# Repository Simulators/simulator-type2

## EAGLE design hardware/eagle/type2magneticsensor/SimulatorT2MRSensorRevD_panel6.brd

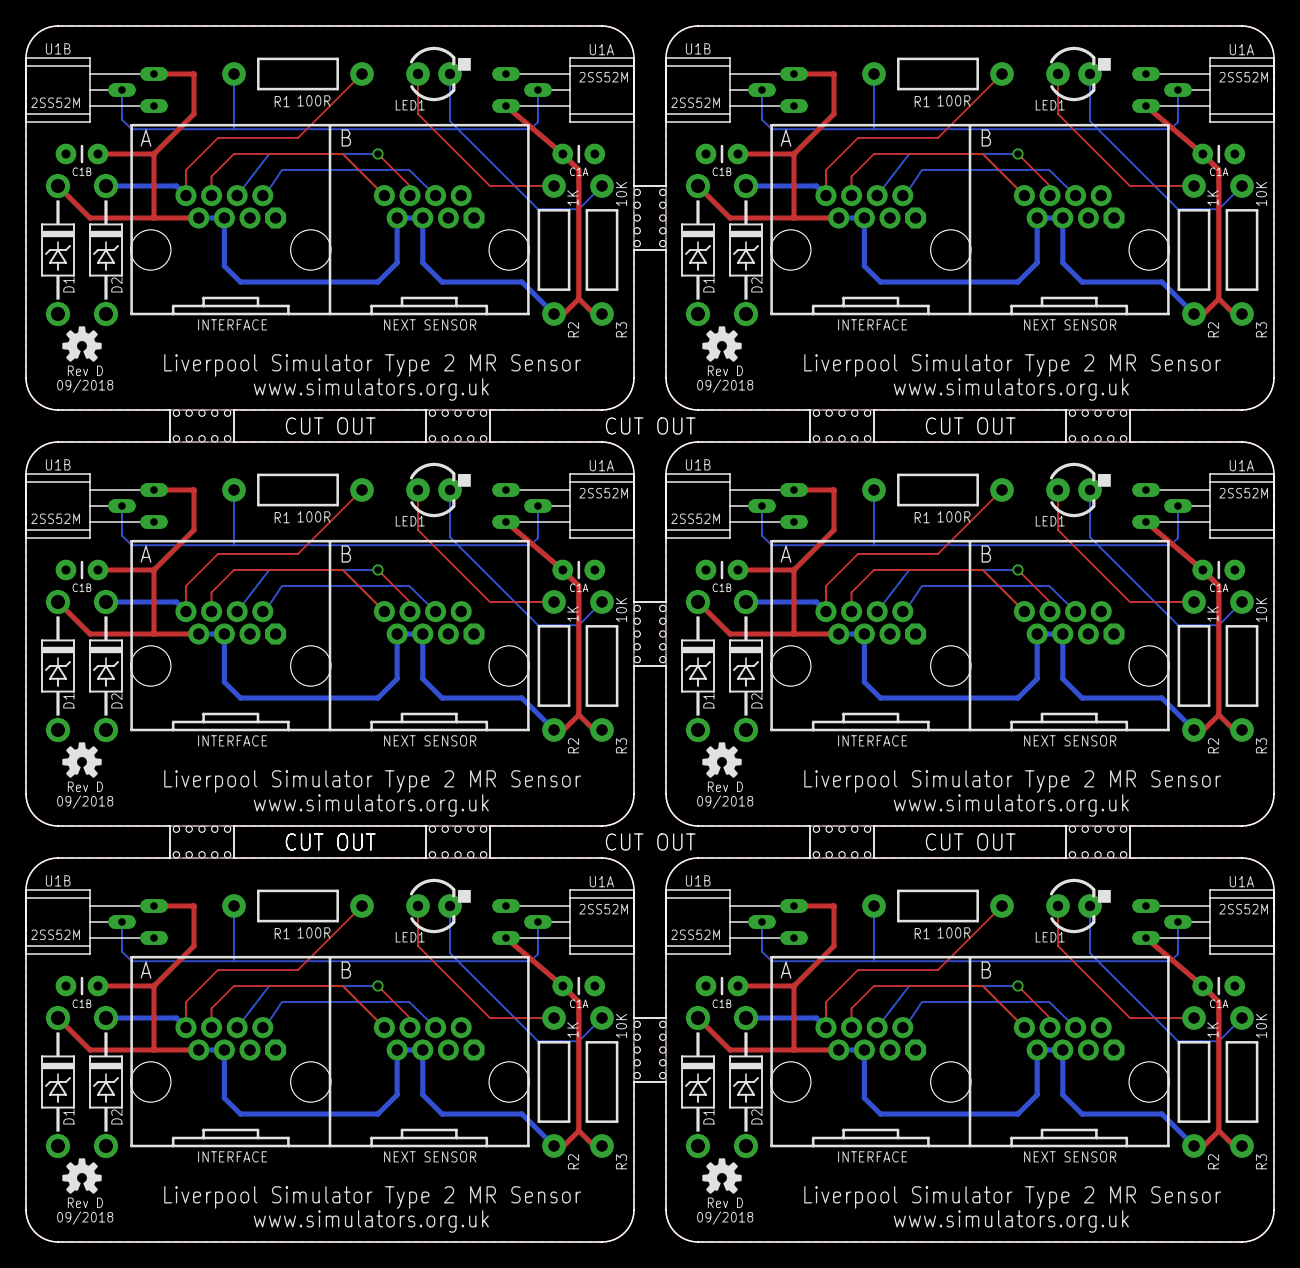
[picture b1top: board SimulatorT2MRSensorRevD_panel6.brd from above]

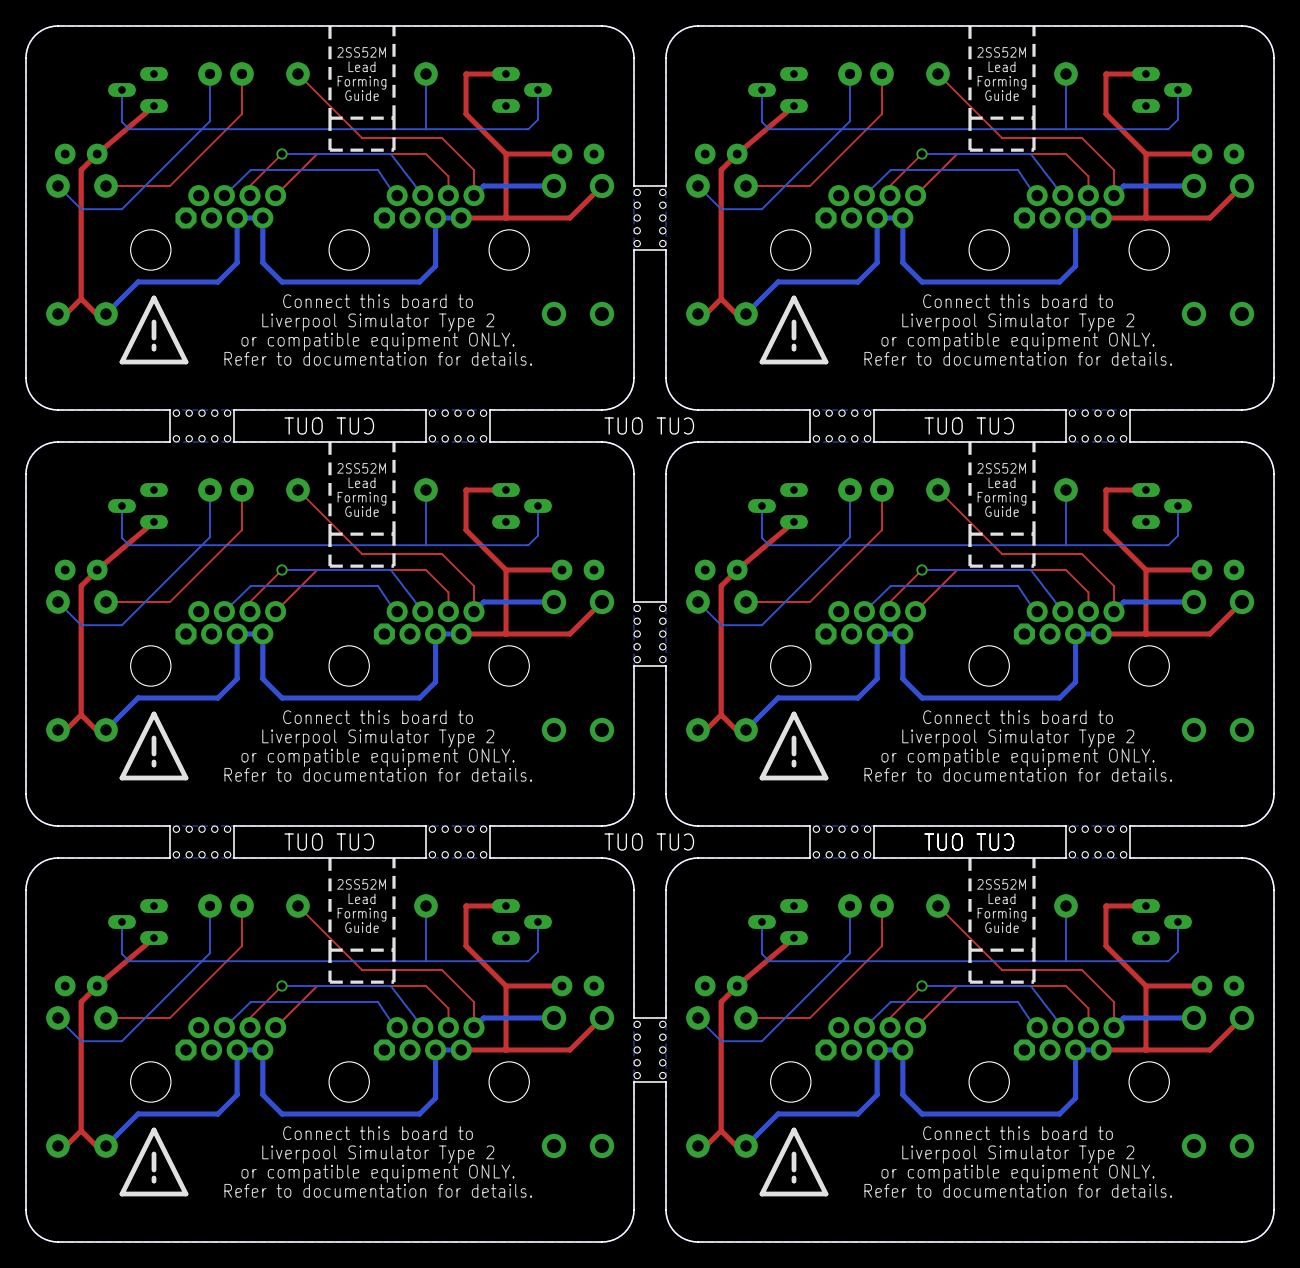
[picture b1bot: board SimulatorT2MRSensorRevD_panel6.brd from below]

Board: 2 copper layers, 99.1 x 96.5 mm, 79 parts (6 on the bottom side), 48 nets.

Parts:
C1A, C1A_1, C1A_2, C1A_3, C1A_4, C1A_5, C1B, C1B_1, C1B_2, C1B_3, C1B_4, C1B_5: 100nF; CAP-PTH-SMALL
D1, D1_1, D1_2, D1_3, D1_4, D1_5, D2, D2_1, D2_2, D2_3, D2_4, D2_5: SA5.0A; DO41_TVS_UNI
E$1, E$2, E$3, E$4, E$5, E$6: WARNING_TRIANGLE_TPLACE
E$12: OUTLINE_PANEL_6_5MM
JP1, JP1_1, JP1_2, JP1_3, JP1_4, JP1_5: RJ45-RJHSE-5080-023HOLE; RJ45-RJHSE-5080-02-3HOLE
LED1, LED1_1, LED1_2, LED1_3, LED1_4, LED1_5: Blue; LED3MM
LOGO1, LOGO1_1, LOGO1_2, LOGO1_3, LOGO1_4, LOGO1_5: OSHW-LOGOS; OSHW-LOGO-S
R1, R1_1, R1_2, R1_3, R1_4, R1_5: 100R; AXIAL-0.4
R2, R2_1, R2_2, R2_3, R2_4, R2_5: 1K; AXIAL-0.4
R3, R3_1, R3_2, R3_3, R3_4, R3_5: 10K; AXIAL-0.4
U1A, U1A_1, U1A_2, U1A_3, U1A_4, U1A_5, U1B, U1B_1, U1B_2, U1B_3, U1B_4, U1B_5: 2SS52MOFFSET; 2SS52M_FLAT_OFFSET

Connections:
!OUT!: D2.CATHODE, JP1.A8, R1.P$1
!OUT!1: D2_1.CATHODE, JP1_1.A8, R1_1.P$1
!OUT!2: D2_2.CATHODE, JP1_2.A8, R1_2.P$1
!OUT!3: D2_3.CATHODE, JP1_3.A8, R1_3.P$1
!OUT!4: D2_4.CATHODE, JP1_4.A8, R1_4.P$1
!OUT!5: D2_5.CATHODE, JP1_5.A8, R1_5.P$1
B2: JP1.A6, JP1.B8
B3: JP1.A4, JP1.B6
B4: JP1.A2, JP1.B4
B21: JP1_1.A6, JP1_1.B8
B22: JP1_2.A6, JP1_2.B8
B23: JP1_3.A6, JP1_3.B8
B24: JP1_4.A6, JP1_4.B8
B25: JP1_5.A6, JP1_5.B8
B31: JP1_1.A4, JP1_1.B6
B32: JP1_2.A4, JP1_2.B6
B33: JP1_3.A4, JP1_3.B6
B34: JP1_4.A4, JP1_4.B6
B35: JP1_5.A4, JP1_5.B6
B41: JP1_1.A2, JP1_1.B4
B42: JP1_2.A2, JP1_2.B4
B43: JP1_3.A2, JP1_3.B4
B44: JP1_4.A2, JP1_4.B4
B45: JP1_5.A2, JP1_5.B4
GND: C1A.2, C1B.2, D1.ANODE, D2.ANODE, JP1.A1, JP1.A3, JP1.B1, JP1.B3, U1A.P$1, U1B.P$1
GND1: C1A_1.2, C1B_1.2, D1_1.ANODE, D2_1.ANODE, JP1_1.A1, JP1_1.A3, JP1_1.B1, JP1_1.B3, U1A_1.P$1, U1B_1.P$1
GND2: C1A_2.2, C1B_2.2, D1_2.ANODE, D2_2.ANODE, JP1_2.A1, JP1_2.A3, JP1_2.B1, JP1_2.B3, U1A_2.P$1, U1B_2.P$1
GND3: C1A_3.2, C1B_3.2, D1_3.ANODE, D2_3.ANODE, JP1_3.A1, JP1_3.A3, JP1_3.B1, JP1_3.B3, U1A_3.P$1, U1B_3.P$1
GND4: C1A_4.2, C1B_4.2, D1_4.ANODE, D2_4.ANODE, JP1_4.A1, JP1_4.A3, JP1_4.B1, JP1_4.B3, U1A_4.P$1, U1B_4.P$1
GND5: C1A_5.2, C1B_5.2, D1_5.ANODE, D2_5.ANODE, JP1_5.A1, JP1_5.A3, JP1_5.B1, JP1_5.B3, U1A_5.P$1, U1B_5.P$1
LED: LED1.A, R2.P$1
LED1: LED1_1.A, R2_1.P$1
LED2: LED1_2.A, R2_2.P$1
LED3: LED1_3.A, R2_3.P$1
LED4: LED1_4.A, R2_4.P$1
LED5: LED1_5.A, R2_5.P$1
SIG: LED1.K, R1.P$2, R3.P$1, U1A.P$2, U1B.P$2
SIG1: LED1_1.K, R1_1.P$2, R3_1.P$1, U1A_1.P$2, U1B_1.P$2
SIG2: LED1_2.K, R1_2.P$2, R3_2.P$1, U1A_2.P$2, U1B_2.P$2
SIG3: LED1_3.K, R1_3.P$2, R3_3.P$1, U1A_3.P$2, U1B_3.P$2
SIG4: LED1_4.K, R1_4.P$2, R3_4.P$1, U1A_4.P$2, U1B_4.P$2
SIG5: LED1_5.K, R1_5.P$2, R3_5.P$1, U1A_5.P$2, U1B_5.P$2
VCC: C1A.1, C1B.1, D1.CATHODE, JP1.A5, JP1.A7, JP1.B5, JP1.B7, R2.P$2, R3.P$2, U1A.P$3, U1B.P$3
VCC1: C1A_1.1, C1B_1.1, D1_1.CATHODE, JP1_1.A5, JP1_1.A7, JP1_1.B5, JP1_1.B7, R2_1.P$2, R3_1.P$2, U1A_1.P$3, U1B_1.P$3
VCC2: C1A_2.1, C1B_2.1, D1_2.CATHODE, JP1_2.A5, JP1_2.A7, JP1_2.B5, JP1_2.B7, R2_2.P$2, R3_2.P$2, U1A_2.P$3, U1B_2.P$3
VCC3: C1A_3.1, C1B_3.1, D1_3.CATHODE, JP1_3.A5, JP1_3.A7, JP1_3.B5, JP1_3.B7, R2_3.P$2, R3_3.P$2, U1A_3.P$3, U1B_3.P$3
VCC4: C1A_4.1, C1B_4.1, D1_4.CATHODE, JP1_4.A5, JP1_4.A7, JP1_4.B5, JP1_4.B7, R2_4.P$2, R3_4.P$2, U1A_4.P$3, U1B_4.P$3
VCC5: C1A_5.1, C1B_5.1, D1_5.CATHODE, JP1_5.A5, JP1_5.A7, JP1_5.B5, JP1_5.B7, R2_5.P$2, R3_5.P$2, U1A_5.P$3, U1B_5.P$3

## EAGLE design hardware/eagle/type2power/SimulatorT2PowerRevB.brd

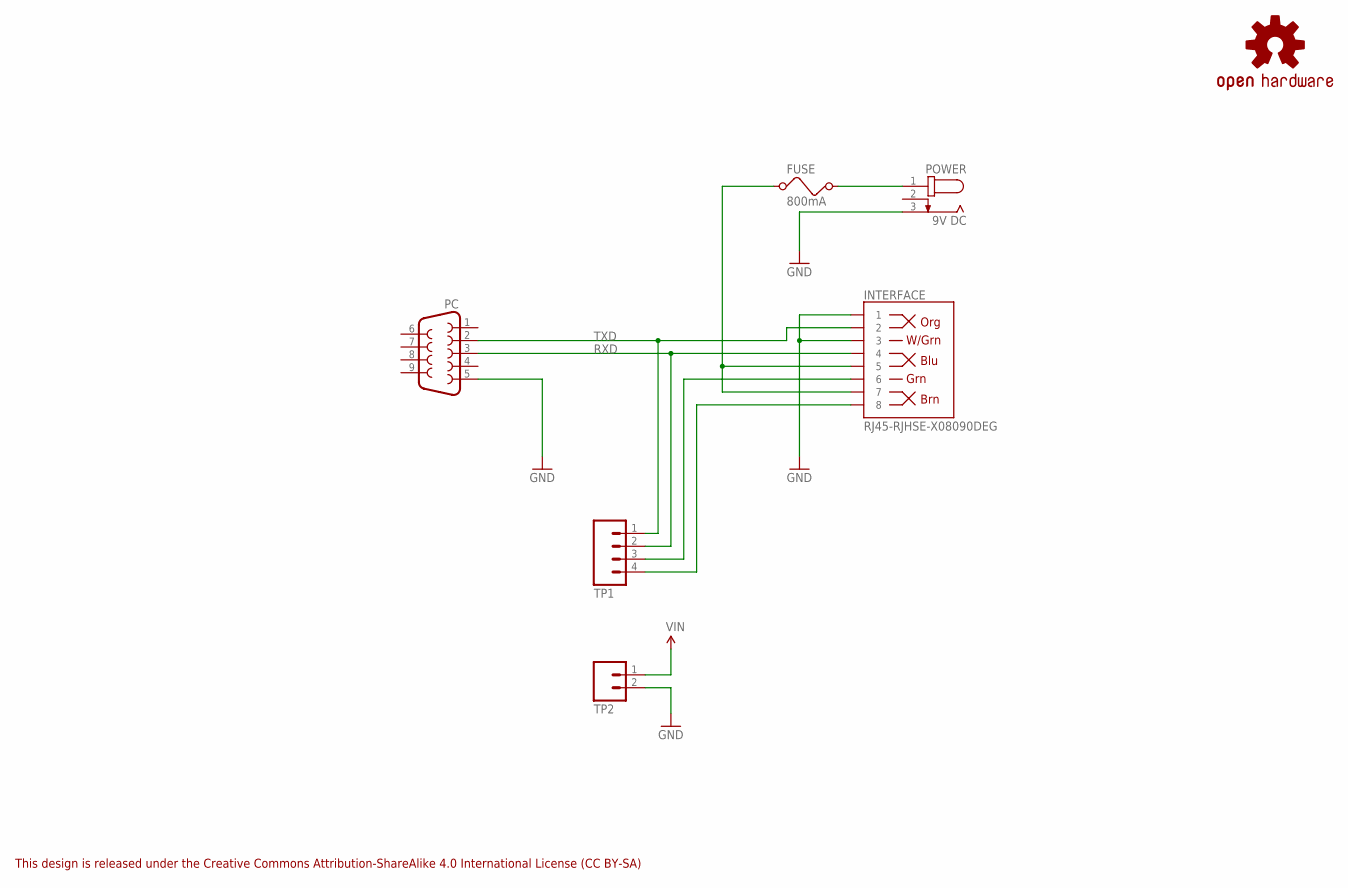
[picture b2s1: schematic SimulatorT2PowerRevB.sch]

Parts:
FUSE: 800mA; MCOMP-FUSE-HOLDER-PCB
INTERFACE: RJ45-RJHSE-X08090DEG; RJ45-RJHSE-5080
LOGO1: OSHW-LOGOS; OSHW-LOGO-S
PC: DB9-CONNECTOR-PCBFEMALE; MULTICOMP-DB9-FEMALE-PCB-90DEG
POWER: 9V DC; CLIFF-FC681465P-DC-JACK
TP1: M04PTH; 1X04
TP2: M02PTH; 1X02

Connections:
GND: INTERFACE.1, INTERFACE.3, PC.5, POWER.3, TP2.2
P6: INTERFACE.6, TP1.3
P8: INTERFACE.8, TP1.4
RXD: INTERFACE.4, PC.3, TP1.2
TXD: INTERFACE.2, PC.2, TP1.1
VIN: FUSE.2, POWER.1, TP2.1
VIN2: FUSE.1, INTERFACE.5, INTERFACE.7

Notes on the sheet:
This design is released under the Creative Commons Attribution-ShareAlike 4.0 International License (CC BY-SA)

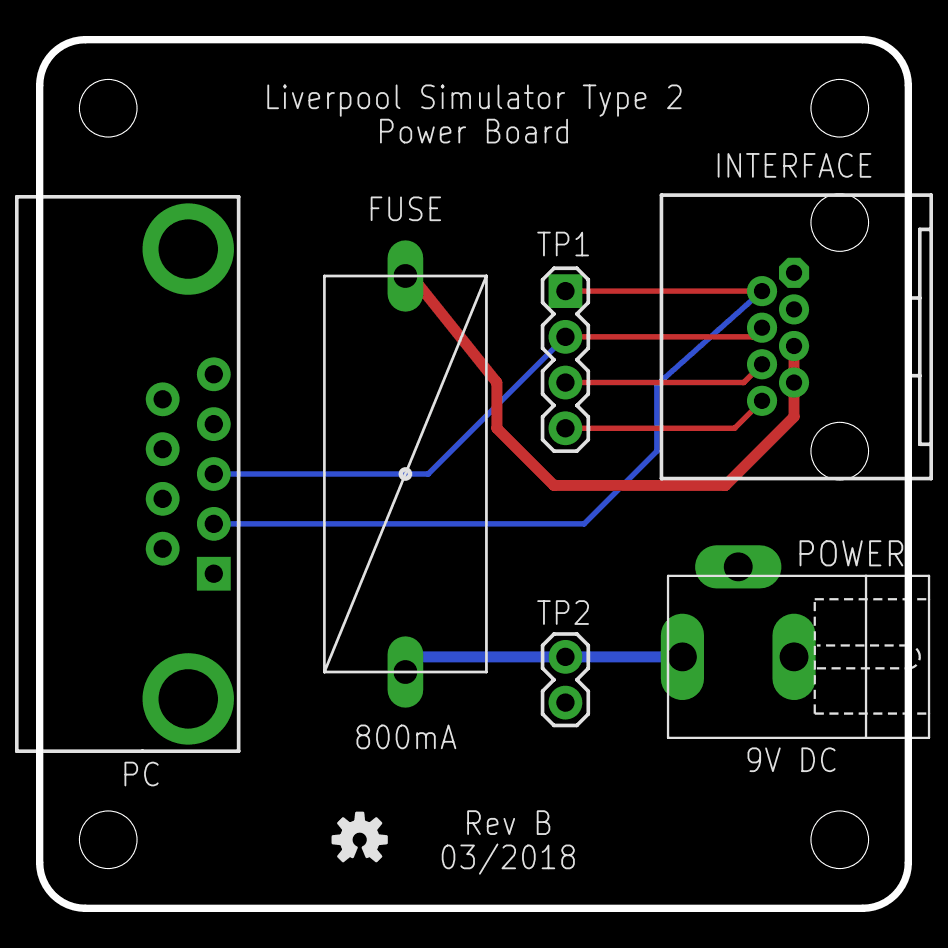
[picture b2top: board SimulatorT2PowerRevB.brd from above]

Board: 2 copper layers, 48.3 x 48.3 mm, 7 parts (0 on the bottom side), 7 nets.

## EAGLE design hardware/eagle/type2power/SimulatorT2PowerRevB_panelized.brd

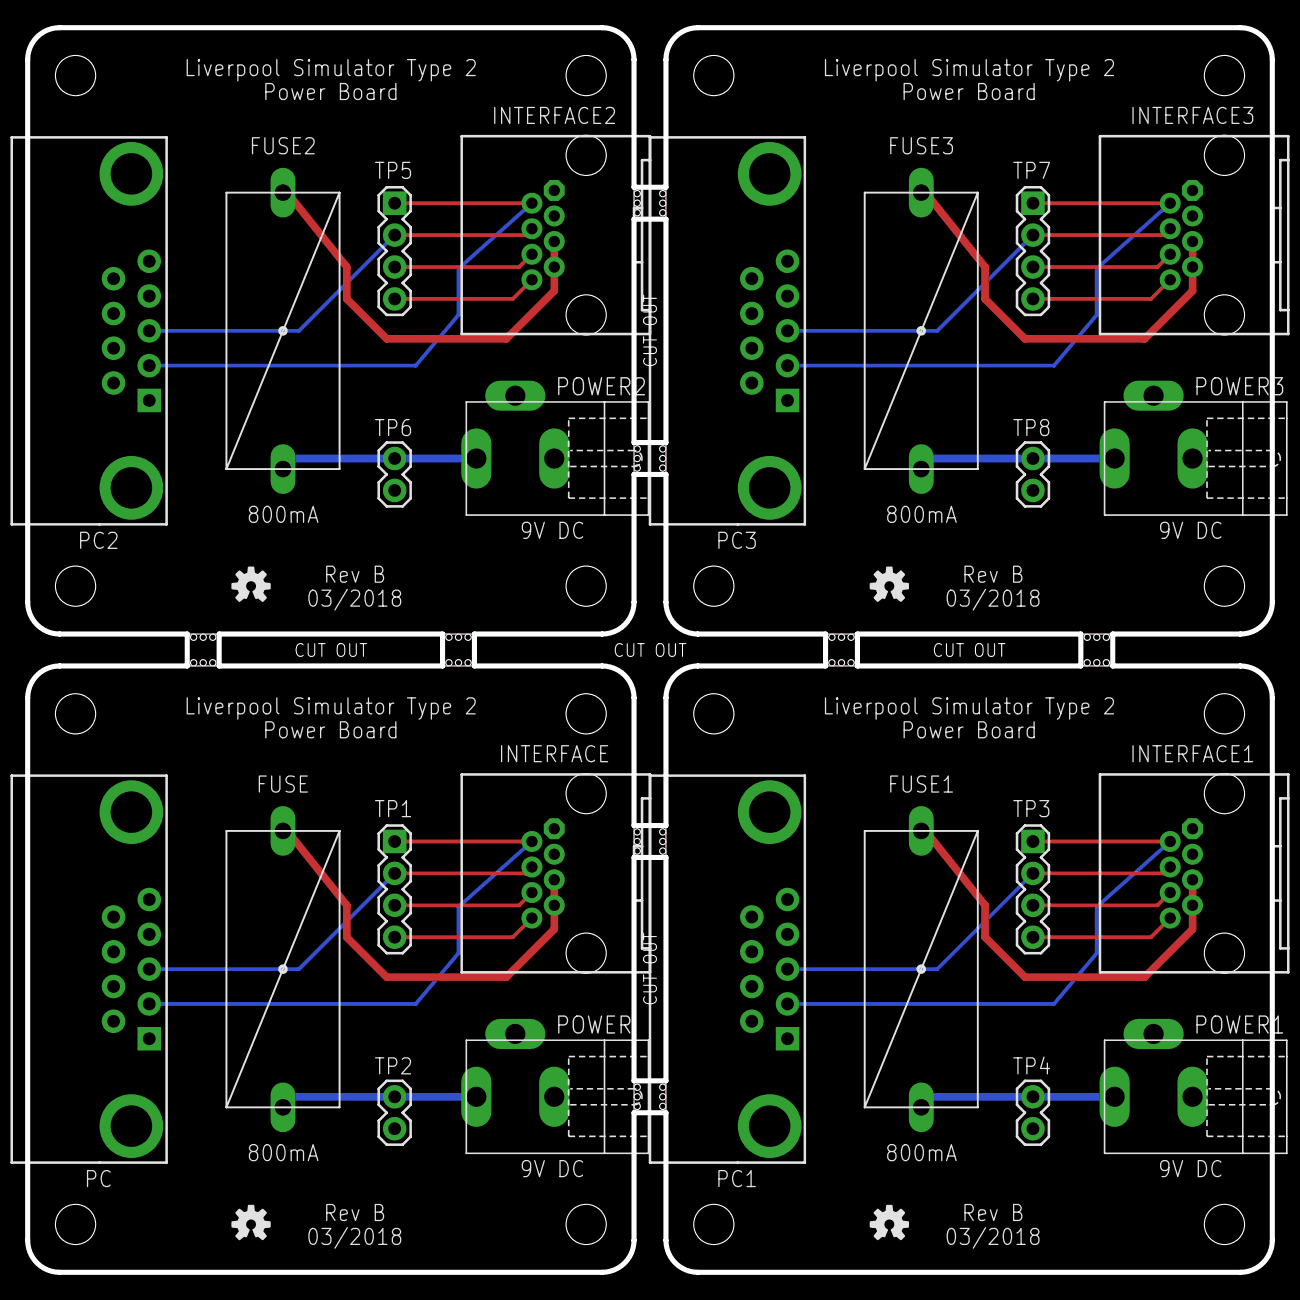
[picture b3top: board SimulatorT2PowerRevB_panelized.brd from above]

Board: 2 copper layers, 99.1 x 99.1 mm, 36 parts (0 on the bottom side), 28 nets.

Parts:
E$1, E$2, E$3, E$4, E$5, E$6, E$7, E$8: STAMP_HOLES
FUSE, FUSE1, FUSE2, FUSE3: 800mA; MCOMP-FUSE-HOLDER-PCB
INTERFACE, INTERFACE1, INTERFACE2, INTERFACE3: RJ45-RJHSE-X08090DEG; RJ45-RJHSE-5080
LOGO1, LOGO2, LOGO3, LOGO4: OSHW-LOGOS; OSHW-LOGO-S
PC, PC1, PC2, PC3: MULTICOMP-DB9-FEMALE-PCB-90DEG
POWER, POWER1, POWER2, POWER3: 9V DC; CLIFF-FC681465P-DC-JACK
TP1, TP3, TP5, TP7: 1X04
TP2, TP4, TP6, TP8: 1X02

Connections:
GND: INTERFACE.1, INTERFACE.3, PC.5, POWER.3, TP2.2
GND1: INTERFACE1.1, INTERFACE1.3, PC1.5, POWER1.3, TP4.2
GND2: INTERFACE2.1, INTERFACE2.3, PC2.5, POWER2.3, TP6.2
GND3: INTERFACE3.1, INTERFACE3.3, PC3.5, POWER3.3, TP8.2
P1: INTERFACE1.6, TP3.3
P2: INTERFACE1.8, TP3.4
P3: INTERFACE2.6, TP5.3
P4: INTERFACE2.8, TP5.4
P5: INTERFACE3.6, TP7.3
P6: INTERFACE.6, TP1.3
P7: INTERFACE3.8, TP7.4
P8: INTERFACE.8, TP1.4
RXD: INTERFACE.4, PC.3, TP1.2
RXD1: INTERFACE1.4, PC1.3, TP3.2
RXD2: INTERFACE2.4, PC2.3, TP5.2
RXD3: INTERFACE3.4, PC3.3, TP7.2
TXD: INTERFACE.2, PC.2, TP1.1
TXD1: INTERFACE1.2, PC1.2, TP3.1
TXD2: INTERFACE2.2, PC2.2, TP5.1
TXD3: INTERFACE3.2, PC3.2, TP7.1
VIN: FUSE.2, POWER.1, TP2.1
VIN1: FUSE1.2, POWER1.1, TP4.1
VIN2: FUSE.1, INTERFACE.5, INTERFACE.7
VIN3: FUSE1.1, INTERFACE1.5, INTERFACE1.7
VIN4: FUSE2.2, POWER2.1, TP6.1
VIN5: FUSE2.1, INTERFACE2.5, INTERFACE2.7
VIN6: FUSE3.2, POWER3.1, TP8.1
VIN7: FUSE3.1, INTERFACE3.5, INTERFACE3.7

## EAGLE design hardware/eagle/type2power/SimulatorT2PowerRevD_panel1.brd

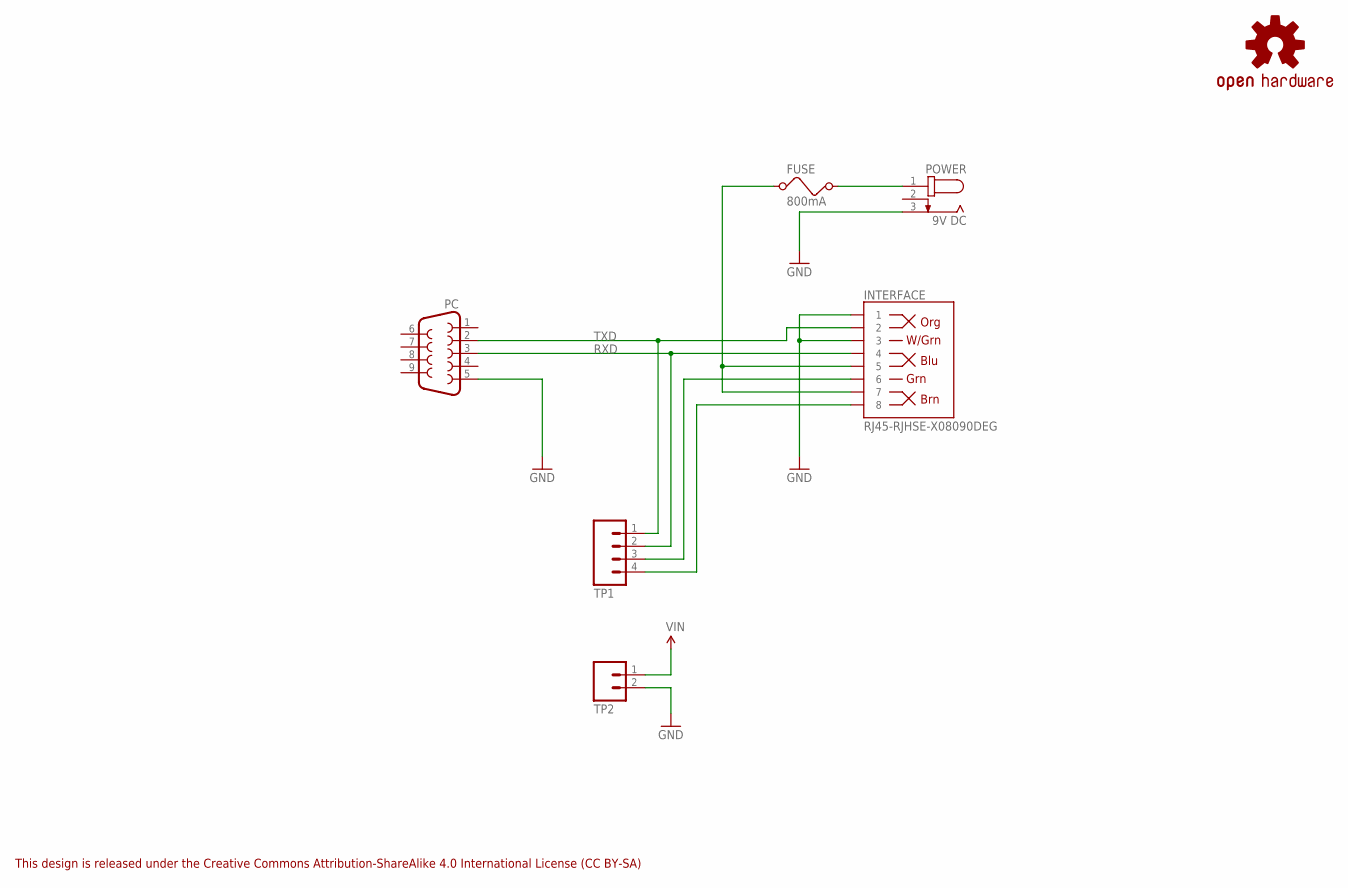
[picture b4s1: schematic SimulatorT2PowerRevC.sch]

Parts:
FUSE: 800mA; MCOMP-FUSE-HOLDER-PCB
INTERFACE: RJ45-RJHSE-X08090DEG; RJ45-RJHSE-5080
LOGO1: OSHW-LOGOS; OSHW-LOGO-S
PC: DB9-CONNECTOR-PCBFEMALE; MULTICOMP-DB9-FEMALE-PCB-90DEG
POWER: 9V DC; CLIFF-FC681465P-DC-JACK
TP1: M04PTH; 1X04
TP2: M02PTH; 1X02

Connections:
GND: INTERFACE.1, INTERFACE.3, PC.5, POWER.3, TP2.2; also elsewhere on the board
P8: INTERFACE.8, TP1.4
RXD: INTERFACE.4, PC.3, TP1.2; also elsewhere on the board
TX2: INTERFACE.6, TP1.3; also elsewhere on the board
TXD: INTERFACE.2, PC.2, TP1.1; also elsewhere on the board
VIN: FUSE.2, POWER.1, TP2.1
VIN2: FUSE.1, INTERFACE.5, INTERFACE.7; also elsewhere on the board

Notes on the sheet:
This design is released under the Creative Commons Attribution-ShareAlike 4.0 International License (CC BY-SA)

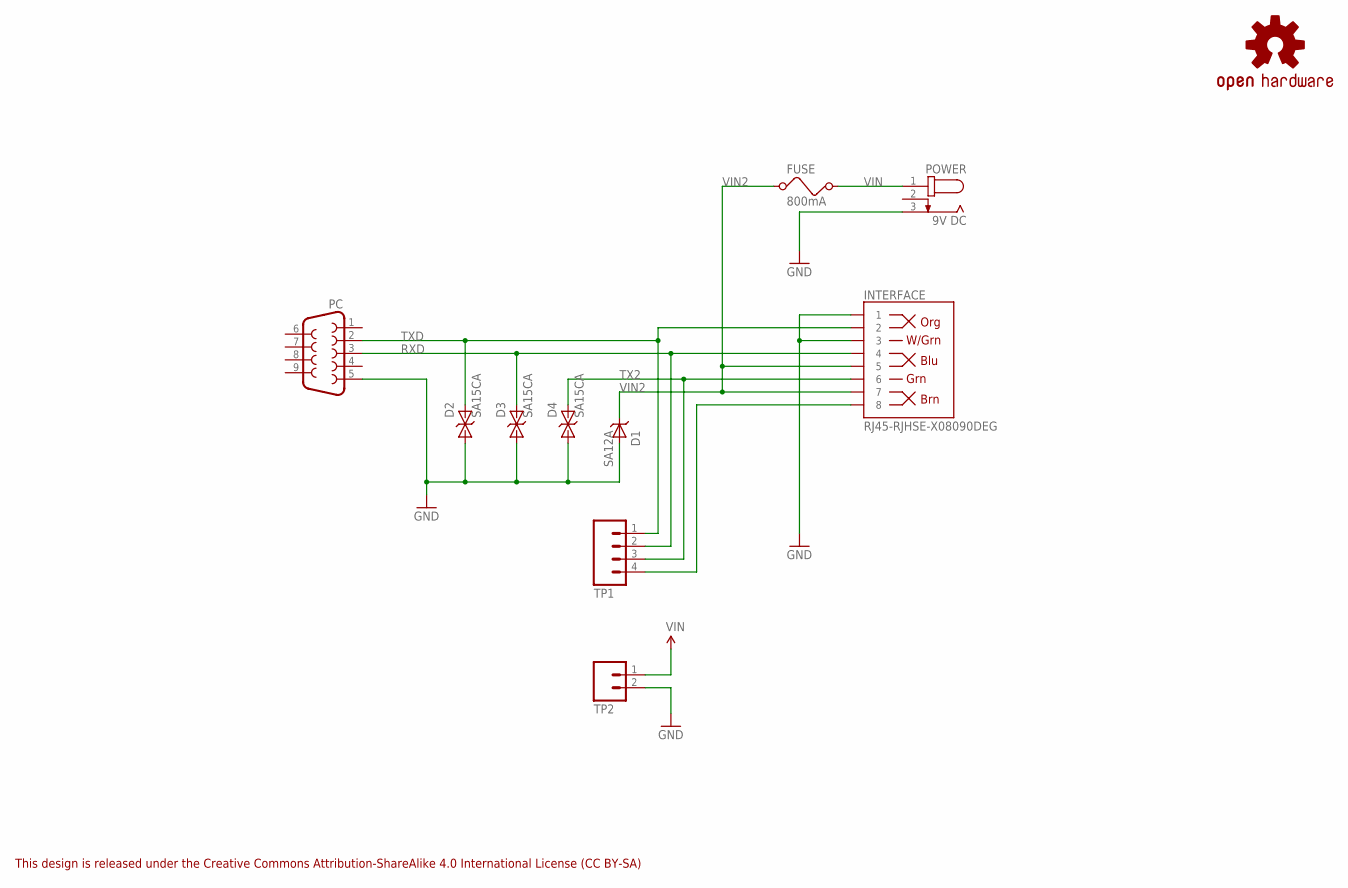
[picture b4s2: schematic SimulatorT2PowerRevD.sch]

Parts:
D1: SA12A; DO41_TVS_UNI
D2, D3, D4: SA15CA; DO41_TVS_BI
FUSE: 800mA; MCOMP-FUSE-HOLDER-PCB
INTERFACE: RJ45-RJHSE-X08090DEG; RJ45-RJHSE-5080
LOGO1: OSHW-LOGOS; OSHW-LOGO-S
PC: DB9-CONNECTOR-PCBFEMALE; MULTICOMP-DB9-FEMALE-PCB-90DEG
POWER: 9V DC; CLIFF-FC681465P-DC-JACK
TP1: M04PTH; 1X04
TP2: M02PTH; 1X02

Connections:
GND: D1.ANODE, D2.A, D3.A, D4.A, INTERFACE.1, INTERFACE.3, PC.5, POWER.3, TP2.2
P8: INTERFACE.8, TP1.4
RXD: D3.C, INTERFACE.4, PC.3, TP1.2
TX2: D4.C, INTERFACE.6, TP1.3
TXD: D2.C, INTERFACE.2, PC.2, TP1.1
VIN: FUSE.2, POWER.1, TP2.1
VIN2: D1.CATHODE, FUSE.1, INTERFACE.5, INTERFACE.7

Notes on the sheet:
This design is released under the Creative Commons Attribution-ShareAlike 4.0 International License (CC BY-SA)

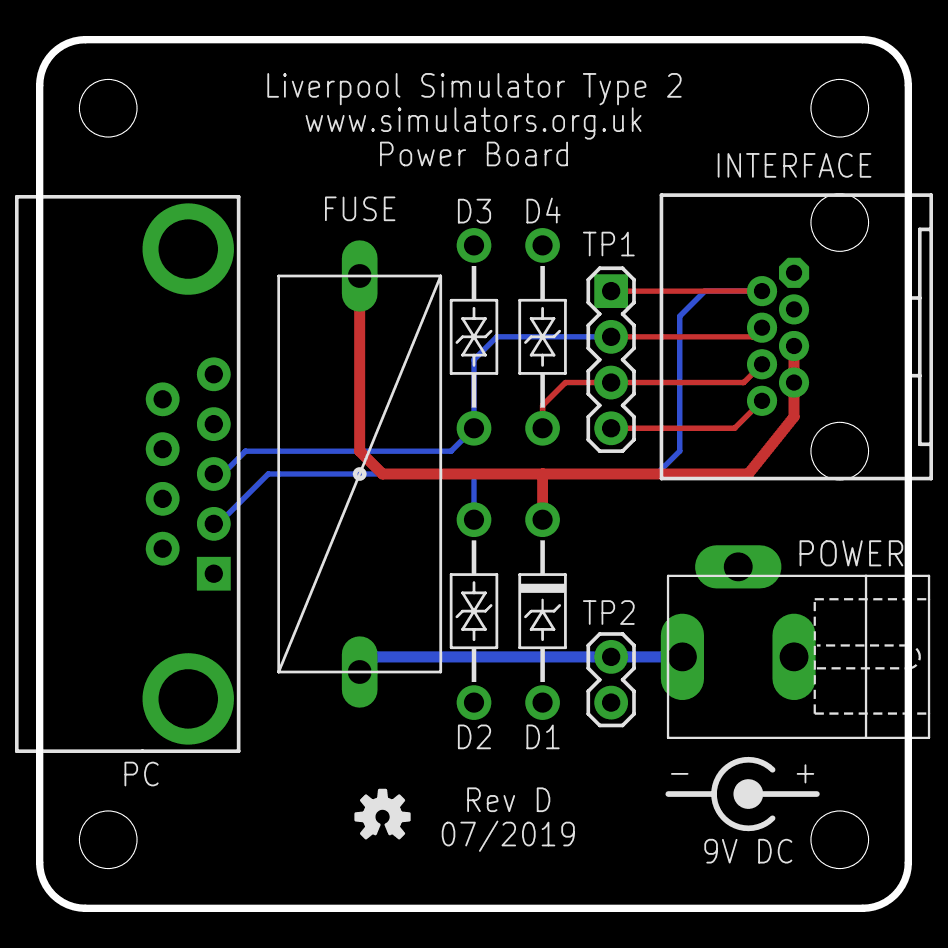
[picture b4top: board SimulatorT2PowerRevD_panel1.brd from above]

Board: 2 copper layers, 48.3 x 48.3 mm, 13 parts (1 on the bottom side), 7 nets.

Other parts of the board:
E$1: WARNING_TRIANGLE_TPLACE
U$1: CENTRE-POS-SILK

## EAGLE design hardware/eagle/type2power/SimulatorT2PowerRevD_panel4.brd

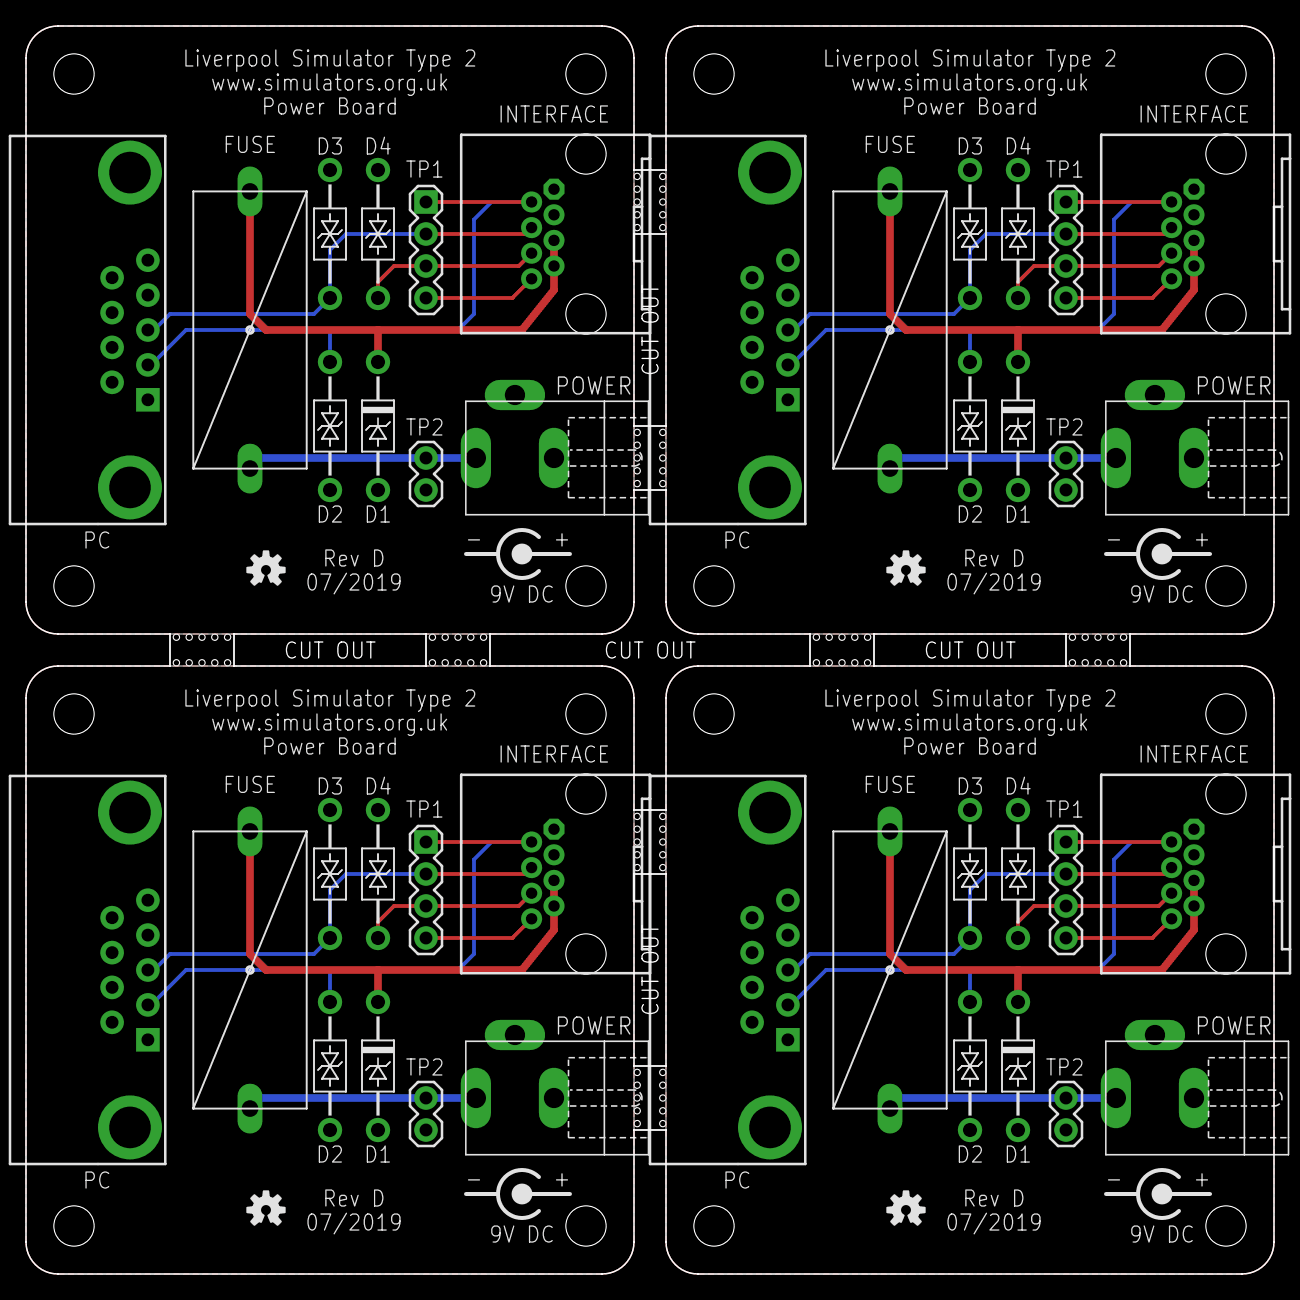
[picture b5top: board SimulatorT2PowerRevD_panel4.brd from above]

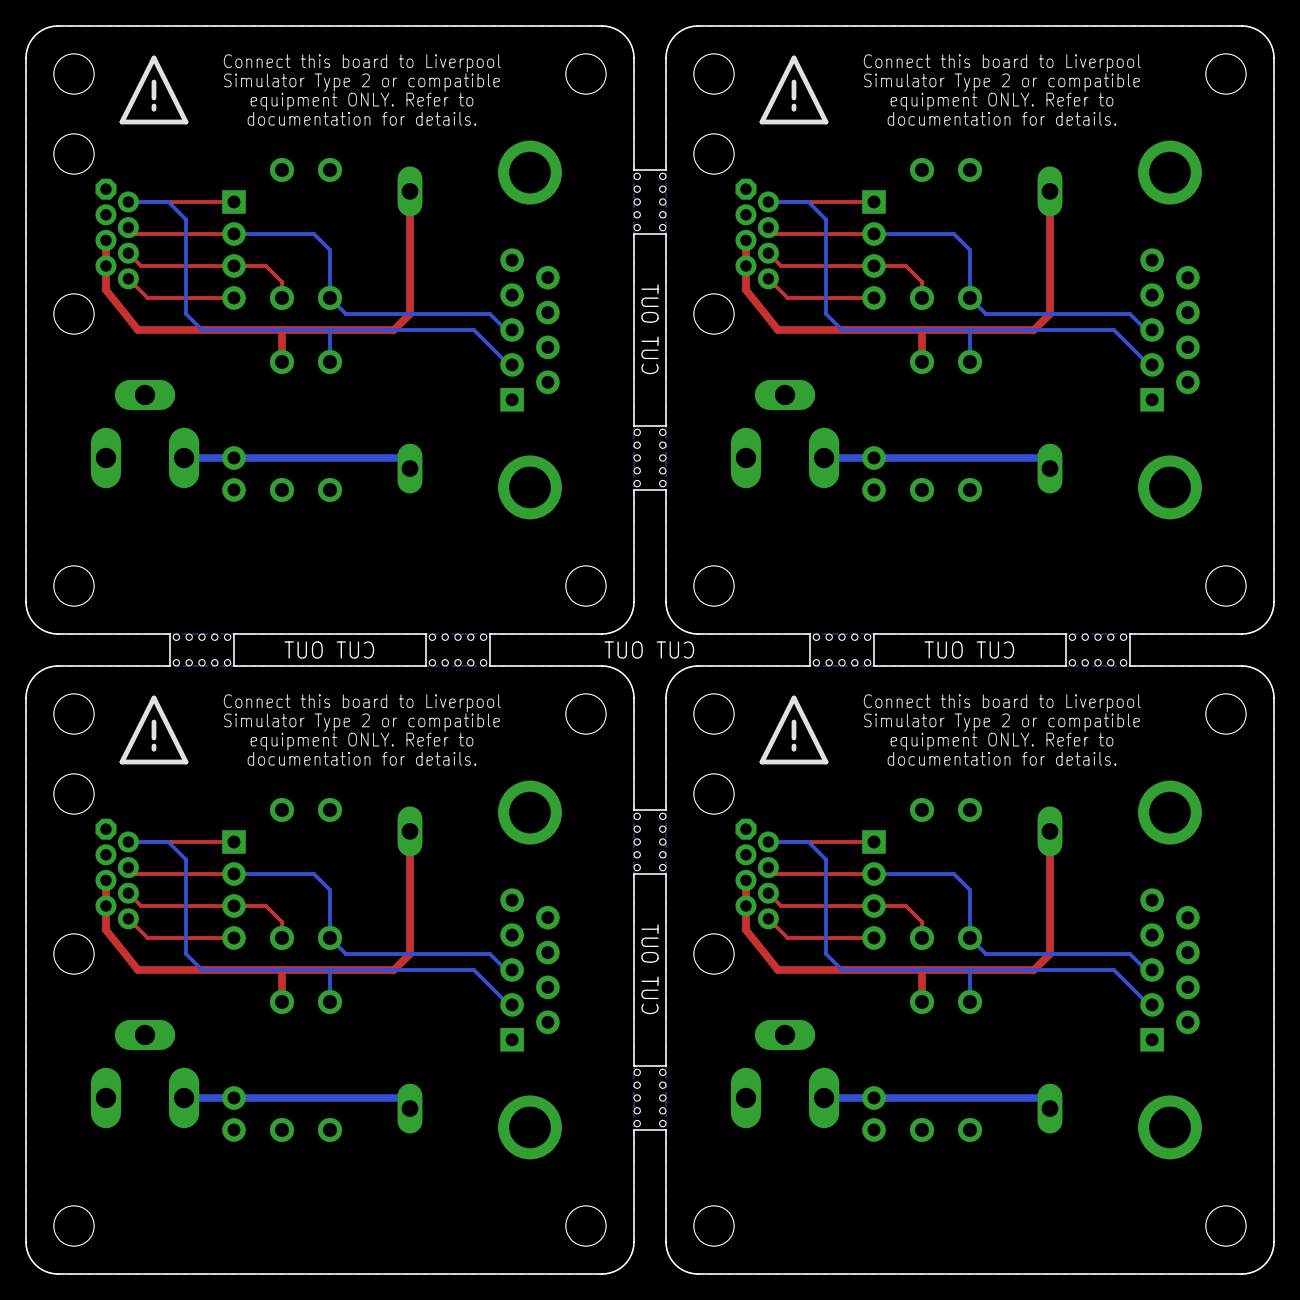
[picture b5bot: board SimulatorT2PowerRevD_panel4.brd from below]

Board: 2 copper layers, 99.1 x 99.1 mm, 53 parts (4 on the bottom side), 28 nets.

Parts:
D1, D1_1, D1_2, D1_3: SA12A; DO41_TVS_UNI
D2, D2_1, D2_2, D2_3, D3, D3_1, D3_2, D3_3, D4, D4_1, D4_2, D4_3: SA15CA; DO41_TVS_BI
E$1, E$3, E$4, E$5: WARNING_TRIANGLE_TPLACE
E$2: OUTLINE_PANEL_4_5MM
FUSE: 800mA; MCOMP-FUSE-HOLDER-PCB
FUSE_1, FUSE_2, FUSE_3: 800mA; MCOMP-FUSE-HOLDER-PCB
INTERFACE: RJ45-RJHSE-X08090DEG; RJ45-RJHSE-5080
INTERFACE_1, INTERFACE_2, INTERFACE_3: RJ45-RJHSE-X08090DEG; RJ45-RJHSE-5080
LOGO1, LOGO1_1, LOGO1_2, LOGO1_3: OSHW-LOGOS; OSHW-LOGO-S
PC: MULTICOMP-DB9-FEMALE-PCB-90DEG
PC_1, PC_2, PC_3: MULTICOMP-DB9-FEMALE-PCB-90DEG
POWER: 9V DC; CLIFF-FC681465P-DC-JACK
POWER_1, POWER_2, POWER_3: 9V DC; CLIFF-FC681465P-DC-JACK
TP1, TP1_1, TP1_2, TP1_3: 1X04
TP2, TP2_1, TP2_2, TP2_3: 1X02
U$1, U$1_1, U$1_2, U$1_3: CENTRE-POS-SILK

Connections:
GND: D1.ANODE, D2.A, D3.A, D4.A, INTERFACE.1, INTERFACE.3, PC.5, POWER.3, TP2.2
GND1: D1_1.ANODE, D2_1.A, D3_1.A, D4_1.A, INTERFACE_1.1, INTERFACE_1.3, PC_1.5, POWER_1.3, TP2_1.2
GND2: D1_2.ANODE, D2_2.A, D3_2.A, D4_2.A, INTERFACE_2.1, INTERFACE_2.3, PC_2.5, POWER_2.3, TP2_2.2
GND3: D1_3.ANODE, D2_3.A, D3_3.A, D4_3.A, INTERFACE_3.1, INTERFACE_3.3, PC_3.5, POWER_3.3, TP2_3.2
P8: INTERFACE.8, TP1.4
P81: INTERFACE_1.8, TP1_1.4
P82: INTERFACE_2.8, TP1_2.4
P83: INTERFACE_3.8, TP1_3.4
RXD: D3.C, INTERFACE.4, PC.3, TP1.2
RXD1: D3_1.C, INTERFACE_1.4, PC_1.3, TP1_1.2
RXD2: D3_2.C, INTERFACE_2.4, PC_2.3, TP1_2.2
RXD3: D3_3.C, INTERFACE_3.4, PC_3.3, TP1_3.2
TX2: D4.C, INTERFACE.6, TP1.3
TX21: D4_1.C, INTERFACE_1.6, TP1_1.3
TX22: D4_2.C, INTERFACE_2.6, TP1_2.3
TX23: D4_3.C, INTERFACE_3.6, TP1_3.3
TXD: D2.C, INTERFACE.2, PC.2, TP1.1
TXD1: D2_1.C, INTERFACE_1.2, PC_1.2, TP1_1.1
TXD2: D2_2.C, INTERFACE_2.2, PC_2.2, TP1_2.1
TXD3: D2_3.C, INTERFACE_3.2, PC_3.2, TP1_3.1
VIN: FUSE.2, POWER.1, TP2.1
VIN1: FUSE_1.2, POWER_1.1, TP2_1.1
VIN2: D1.CATHODE, FUSE.1, INTERFACE.5, INTERFACE.7
VIN3: FUSE_2.2, POWER_2.1, TP2_2.1
VIN4: FUSE_3.2, POWER_3.1, TP2_3.1
VIN21: D1_1.CATHODE, FUSE_1.1, INTERFACE_1.5, INTERFACE_1.7
VIN22: D1_2.CATHODE, FUSE_2.1, INTERFACE_2.5, INTERFACE_2.7
VIN23: D1_3.CATHODE, FUSE_3.1, INTERFACE_3.5, INTERFACE_3.7

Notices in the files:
parts and their libraries:
SparkFun-Aesthetics: Licensing: Creative Commons ShareAlike 4.0 International - https://creativecommons.org/licenses/by-sa/4.0
